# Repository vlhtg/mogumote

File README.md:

# mogumote

Simple WiFi remote based of my TLT framework

Hardware - v0.1 done

Software - WIP

Obviously, the general shape of the PCB is NOT my creation, but it is actually taken from the well-known game Among Us. This project acts as a tribute to that.

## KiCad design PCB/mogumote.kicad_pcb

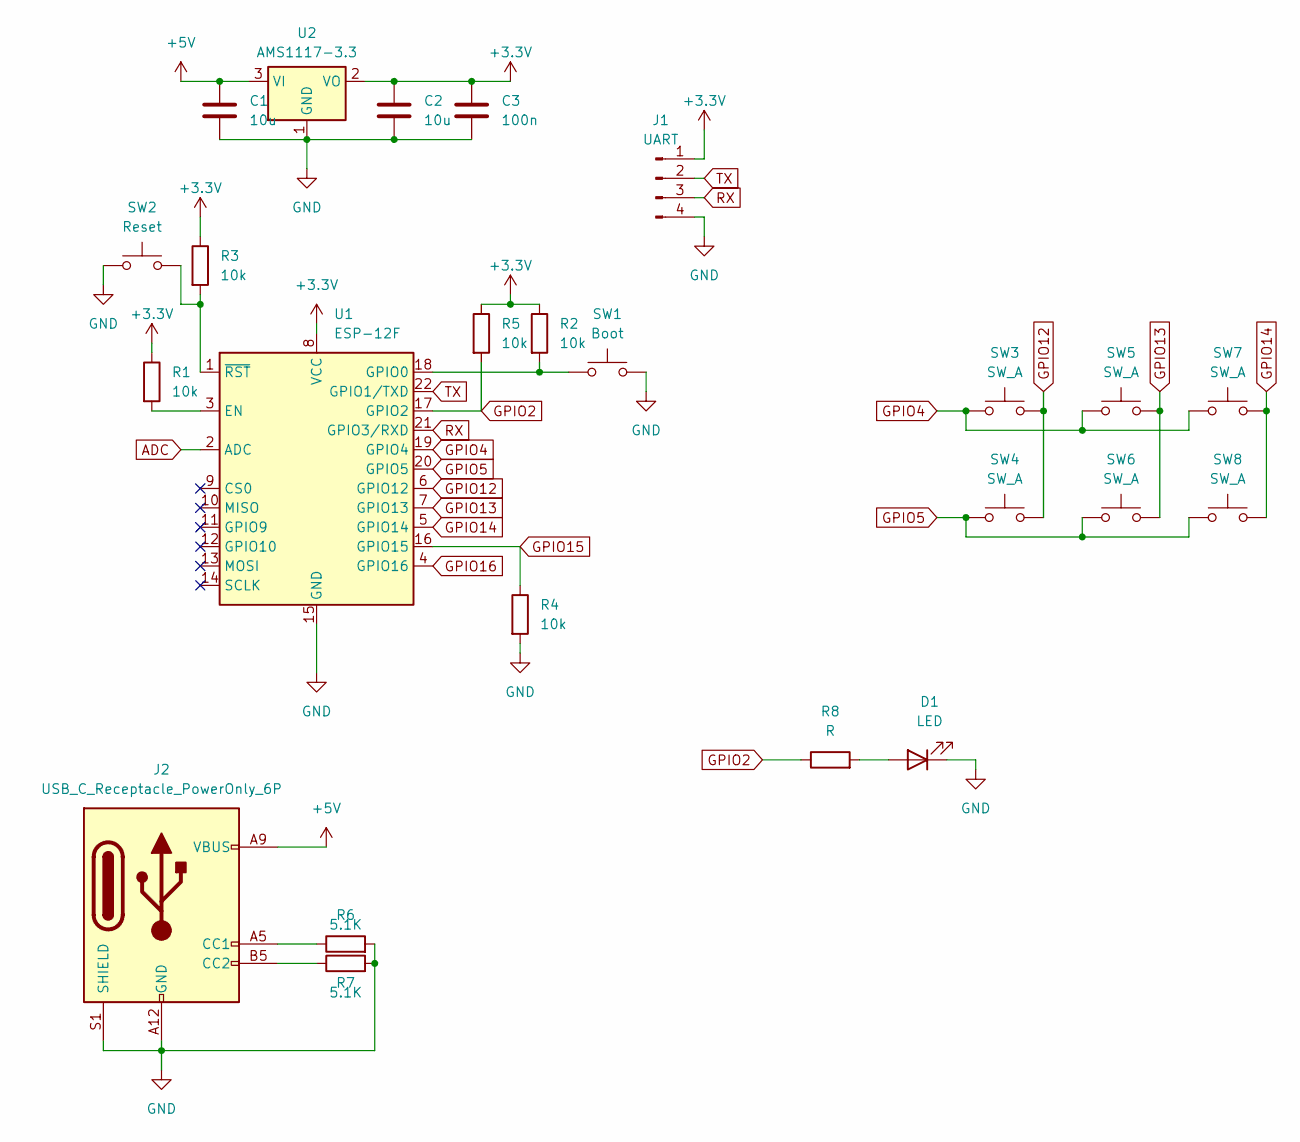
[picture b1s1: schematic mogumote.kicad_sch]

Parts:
C1, C2: 10u; C_0805_2012Metric_Pad1.18x1.45mm_HandSolder
C3: 100n; C_0805_2012Metric_Pad1.18x1.45mm_HandSolder
D1: LED; LED_0603_1608Metric_Pad1.05x0.95mm_HandSolder
J1: UART; JST_XH_B4B-XH-A_1x04_P2.50mm_Vertical
J2: USB_C_Receptacle_PowerOnly_6P; USB_C_Receptacle_GCT_USB4125-xx-x-0190_6P_TopMnt_Horizontal
R1, R2, R3, R4, R5: 10k; R_0805_2012Metric_Pad1.20x1.40mm_HandSolder
R6, R7: 5.1K; C_0805_2012Metric_Pad1.18x1.45mm_HandSolder
R8: R; R_0805_2012Metric_Pad1.20x1.40mm_HandSolder
SW1: Boot; SW_Push_1P1T_NO_6x6mm_H9.5mm
SW2: Reset; SW_Push_1P1T_NO_6x6mm_H9.5mm
SW3, SW4, SW5, SW6, SW7, SW8: SW_A; SW_Push_1P1T_NO_6x6mm_H9.5mm
U1: ESP-12F; ESP-12E
U2: AMS1117-3.3; SOT-223-3_TabPin2

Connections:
+3.3V: C2.1, C3.1, J1.1, R1.1, R2.1, R3.1, R5.1, U1.8 (VCC), U2.2 (VO)
+5V: C1.1, J2.A9 (VBUS), J2.B9 (VBUS), U2.3 (VI)
ADC: U1.2 (ADC)
GND: C1.2, C2.2, C3.2, D1.1 (K), J1.4, J2.A12 (GND), J2.B12 (GND), J2.S1 (SHIELD), R4.2, R6.2, R7.2, SW1.2, SW2.1, U1.15 (GND), U2.1 (GND)
GPIO2: R5.2, R8.1, U1.17 (GPIO2)
GPIO4: SW3.1, SW5.1, SW7.1, U1.19 (GPIO4)
GPIO5: SW4.1, SW6.1, SW8.1, U1.20 (GPIO5)
GPIO12: SW3.2, SW4.2, U1.6 (GPIO12)
GPIO13: SW5.2, SW6.2, U1.7 (GPIO13)
GPIO14: SW7.2, SW8.2, U1.5 (GPIO14)
GPIO15: R4.1, U1.16 (GPIO15)
GPIO16: U1.4 (GPIO16)
unnamed: D1.2 (A), R8.2
unnamed: J2.A5 (CC1), R6.1
unnamed: J2.B5 (CC2), R7.1
unnamed: R1.2, U1.3 (EN)
unnamed: R2.2, SW1.1, U1.18 (GPIO0)
unnamed: R3.2, SW2.2, U1.1 (~RST)
RX: J1.3, U1.21 (GPIO3/RXD)
TX: J1.2, U1.22 (GPIO1/TXD)

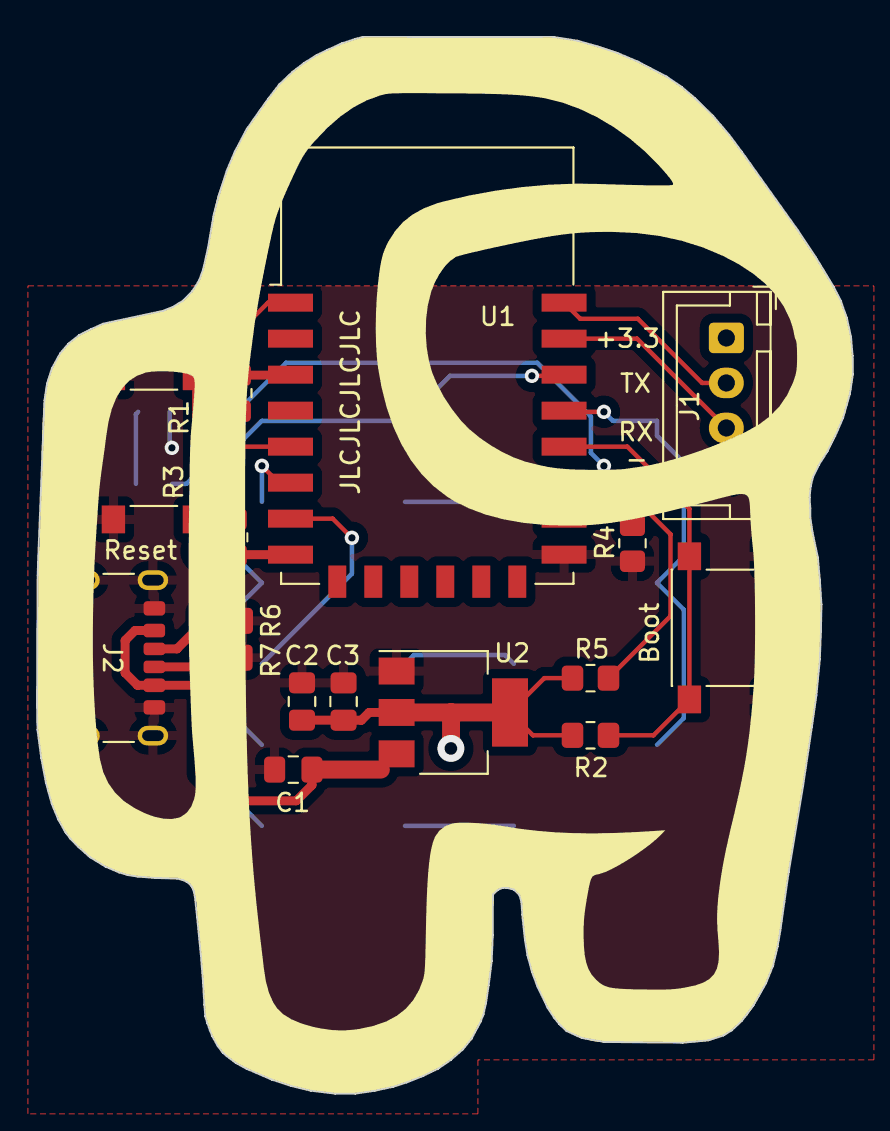
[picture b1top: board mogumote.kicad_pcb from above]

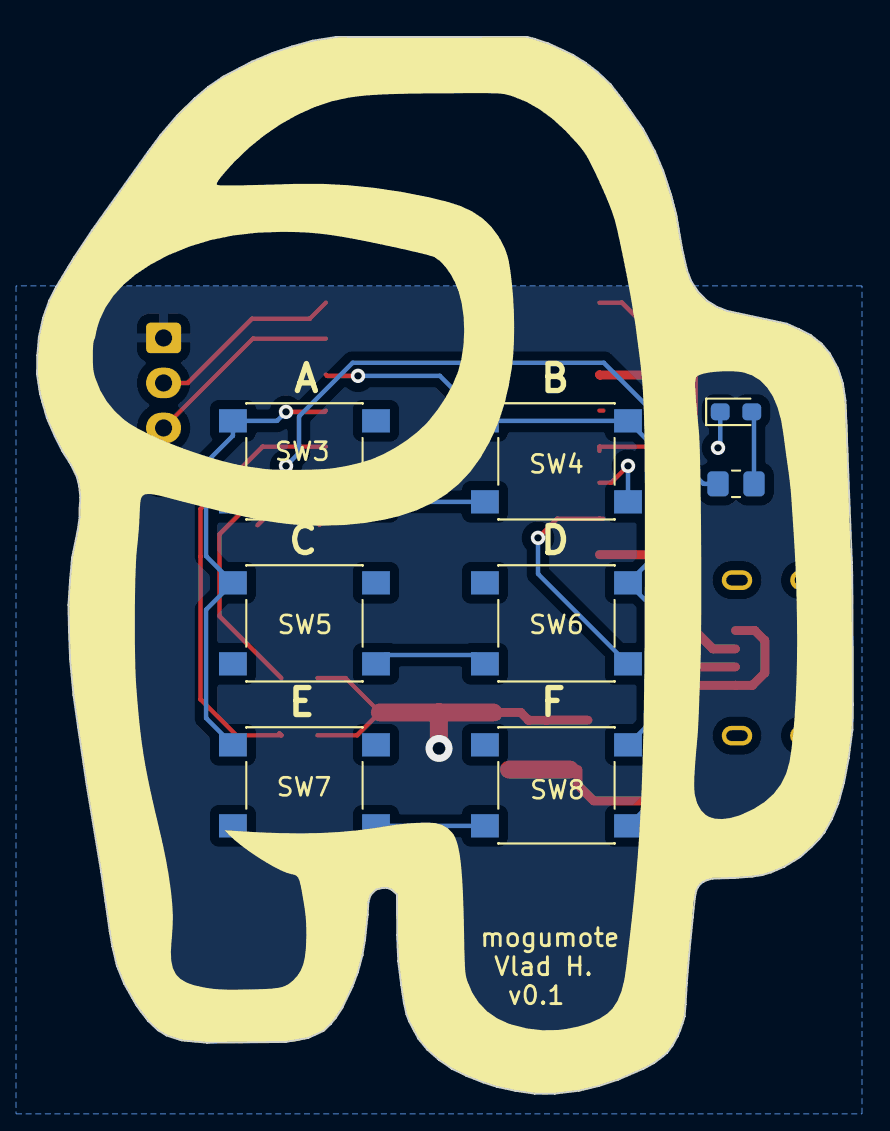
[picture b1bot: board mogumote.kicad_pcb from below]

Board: 2 copper layers, 45.3 x 58.7 mm, 24 parts (8 on the bottom side), 18 nets.

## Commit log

2023-12-16 Added v0.1 PCB files
2023-12-16 Added information
2023-12-16 Added disclaimer
2023-12-16 Formatting
